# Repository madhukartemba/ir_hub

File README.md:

# IR Hub

A self-contained, open-source smart IR universal remote built around the ESP8266. IR Hub learns the codes from your existing TV/AC/audio remotes, stores them locally, and lets you fire them from a physical button, an on-device menu, Home Assistant (MQTT), or Alexa — all over your home Wi-Fi.

It ships as a complete hardware + firmware project: custom KiCad PCB, 3D-printed enclosure, and PlatformIO firmware with OTA updates.

- **Help (web preview):** https://ir-hub.pages.dev/help
- **Help (markdown source):** [`docs/HELP.md`](docs/HELP.md)
- **Release / OTA notes:** [`docs/RELEASE.md`](docs/RELEASE.md)

---

## What It Does

- **Learns IR remotes.** Point any IR remote at the receiver, press a button, and the Hub stores the raw signal.
- **Replays IR commands.** 8x parallel high-current IR LEDs give very long range so the Hub can sit across the room from the appliance.
- **Smart home bridge.** Each learned device shows up as an MQTT entity (works great with Home Assistant) and as an Alexa-controllable device (via Espalexa).
- **Standalone UI.** 128x64 OLED + single button + 30-LED NeoPixel ring + haptic motor + buzzer. No phone required for day-to-day use.
- **Captive-portal Wi-Fi setup.** First boot exposes an `IRHub V3 Setup` AP; users join it and configure Wi-Fi + MQTT from their phone.
- **OTA updates.** Cloud OTA (via Cloudflare Pages manifest, polled hourly) and LAN OTA (ArduinoOTA + mDNS auto-discovery).
- **Safe boot.** Boot-loop counter + LittleFS format-on-failure recovery so a bad save never bricks the device.

---

## Hardware Variants

**Only `v3` (the custom PCB build) is actively supported.** The older `v0` (NodeMCU perfboard) and `v1` (D1 Mini perfboard) variants still exist in the codebase as historical prototypes, but they are **deprecated** — no longer maintained, no longer released, and not recommended for new builds.

The rest of this README only covers v3.

---

## Bill of Materials (v3)

Full BOM with LCSC-style designators lives in [`PCB/IRHub_PCB_V3/production/bom.csv`](PCB/IRHub_PCB_V3/production/bom.csv). The major active parts:

| Block | Part | Role |
|---|---|---|
| MCU | **ESP-12F** (ESP8266) | Brains + Wi-Fi |
| USB | **USB-C receptacle + CH340C** | USB-UART for programming and 5 V power |
| Power | **AMS1117-3.3** LDO | 5 V -> 3.3 V regulation |
| Display | **OLED-128O064D** (SH1106, I²C) | 128x64 status/menu screen |
| LEDs | **30x WS2812B-2020** | Circular addressable RGB ring |
| IR TX | **8x IR204A** + UMH3N driver + AO3400A MOSFET | High-current IR blaster array |
| IR RX | **TSOP382xx** | 38 kHz IR demodulator for learning |
| Haptics | **DRV2605L** + external LRA (JST connector) | Tactile click feedback |
| Audio | **CMT-7525-80-SMT-TR** magnetic buzzer | UI beeps / chimes |
| Input | **Single tactile push button** | All UI navigation |

Plus passives, test points, and the JST-SH connector for the LRA.

---

## How To Build One (v3)

### 1. Order the PCB

KiCad project: [`PCB/IRHub_PCB_V3/`](PCB/IRHub_PCB_V3/)

- Source schematic + board: `IRHub_V3.kicad_sch`, `IRHub_V3.kicad_pcb`
- Manufacturing bundle: [`PCB/IRHub_PCB_V3/production/IR_Hub_3.zip`](PCB/IRHub_PCB_V3/production/IR_Hub_3.zip) (gerbers + drills, ready to upload to JLCPCB / PCBWay / OSHPark)
- For JLCPCB-style PCBA also use: `production/bom.csv` + `production/positions.csv`
- 3D preview / STEP: `IRHub_V3.step` and `IRHub_V3_Model.step`

Default board specs are 2-layer, 1.6 mm, HASL — anything in that ballpark from any low-cost fab works fine.

### 2. Print the Enclosure

3D-printable enclosure parts for the v3 PCB live in [`3D Print/Version 3/`](3D%20Print/Version%203/):

- `Base.stl` — main housing the PCB drops into
- `Top Cover.stl` — top shell with the OLED + button cutouts
- `Led Ring.stl` — diffuser ring that sits over the WS2812 ring

Plus the full Fusion 360 source as `IR Hub V3 v74.f3z`, and ready-to-print GCode under `3D Print/Version 3/GCode/`.

Recommended print settings: PLA, 0.2 mm layer height, 15–20% infill, supports off for `Top Cover` (geometry is overhang-friendly).

### 3. Assemble

1. Solder the PCB (or order PCBA). If hand-soldering, start with the QFP / SMD parts (CH340C, AMS1117, DRV2605L), then passives, then through-hole IR LEDs and the button, then the WS2812 ring last so it doesn't get cooked.
2. Verify 3.3 V on test point `TP9` and 5 V on `5V1` *before* installing the ESP-12F.
3. Solder/clip in the OLED, plug the LRA into the JST-SH connector.
4. Drop the populated PCB into the printed `Base`, screw on `Top Cover`, slip `Led Ring` over the LEDs.

### 4. Flash the Firmware

You only need to do this once — after that, OTA updates take over.

1. Install **PlatformIO** (VS Code extension or `pip install platformio`).
2. Clone this repo and open it in PlatformIO.
   ```bash
   git clone https://github.com/madhukartemba/ir_hub.git
   cd ir_hub
   ```
3. Create your `include/secrets.h` from the template:
   ```bash
   cp include/secrets.h.example include/secrets.h
   ```
   Edit it to set (all optional, but recommended):
   - `MQTT_HOST` / `MQTT_USER` / `MQTT_PASSWORD` — Home Assistant broker.
   - `OTA_PASSWORD` — required for LAN OTA pushes.
   - `OTA_MANIFEST_URL` — your Cloudflare Pages manifest URL (only needed if you fork and self-host releases).
4. Plug the assembled board into USB-C and run:
   ```bash
   pio run -e ir_hub_version_3 -t upload
   ```
5. Open the serial monitor to see boot logs:
   ```bash
   pio device monitor -b 115200
   ```

That's it — the rest of the configuration (Wi-Fi, MQTT credentials, learned remotes) happens on-device.

### 5. Power On & Configure

On first boot the Hub shows `IR Hub — Ready! (Offline)` and starts a captive-portal AP called **`IRHub V3 Setup`**. Connect a phone to it and the captive portal walks you through Wi-Fi (and optional MQTT) setup. From there, see the [User Help Guide](docs/HELP.md) for adding remotes, using Alexa, etc.

---

## Pinout (v3)

For reference, defined in [`src/config.h`](src/config.h):

| Function | ESP-12F Pin |
|---|---|
| Button | D0 |
| OLED SCL | D1 |
| OLED SDA | D2 |
| Buzzer | D3 |
| IR Receiver | D5 |
| IR Transmitter | D6 |
| NeoPixel ring | D7 |

---

## Project Layout

```
ir_hub/
  src/                Firmware entry + UI screens
  lib/                Internal libraries (IR, MQTT, Display, OtaUpdater, etc.)
  include/            Project headers + secrets template
  PCB/                KiCad sources + gerbers + production BOM (v3; v1 archived)
  3D Print/           Fusion sources + STL + GCode for enclosures
  docs/               User help, release/OTA documentation
  scripts/            Release automation + local OTA upload helper
  ota/                Public OTA manifest served via Cloudflare Pages
  binaries/           Signed firmware images served via Cloudflare Pages
```

---

## For Developers

All commands target v3 — the older `v0` / `v1` PlatformIO envs are deprecated and not part of the release pipeline.

- **Build:** `pio run -e ir_hub_version_3`
- **Cut a release:** `python3 scripts/release.py 1.2.3` — bumps `custom_firmware_version`, builds `ir_hub_version_3`, stages the binary under `binaries/`, updates `ota/manifest.json`, commits + pushes. See [`docs/RELEASE.md`](docs/RELEASE.md) for the full flow.
- **LAN OTA push:** `python3 scripts/local_upload_ota.py -e ir_hub_version_3 --discover` — mDNS-discovers `ir-hub-*` devices and pushes the current build over the network. Password is read from `include/secrets.h`.

---

## License

MIT — see `LICENSE` (or use the source freely; attribution appreciated).

---

<div align="center">
  Made by <a href="mailto:madhusmiles.madhukar@gmail.com">Madhukar Temba</a>
</div>

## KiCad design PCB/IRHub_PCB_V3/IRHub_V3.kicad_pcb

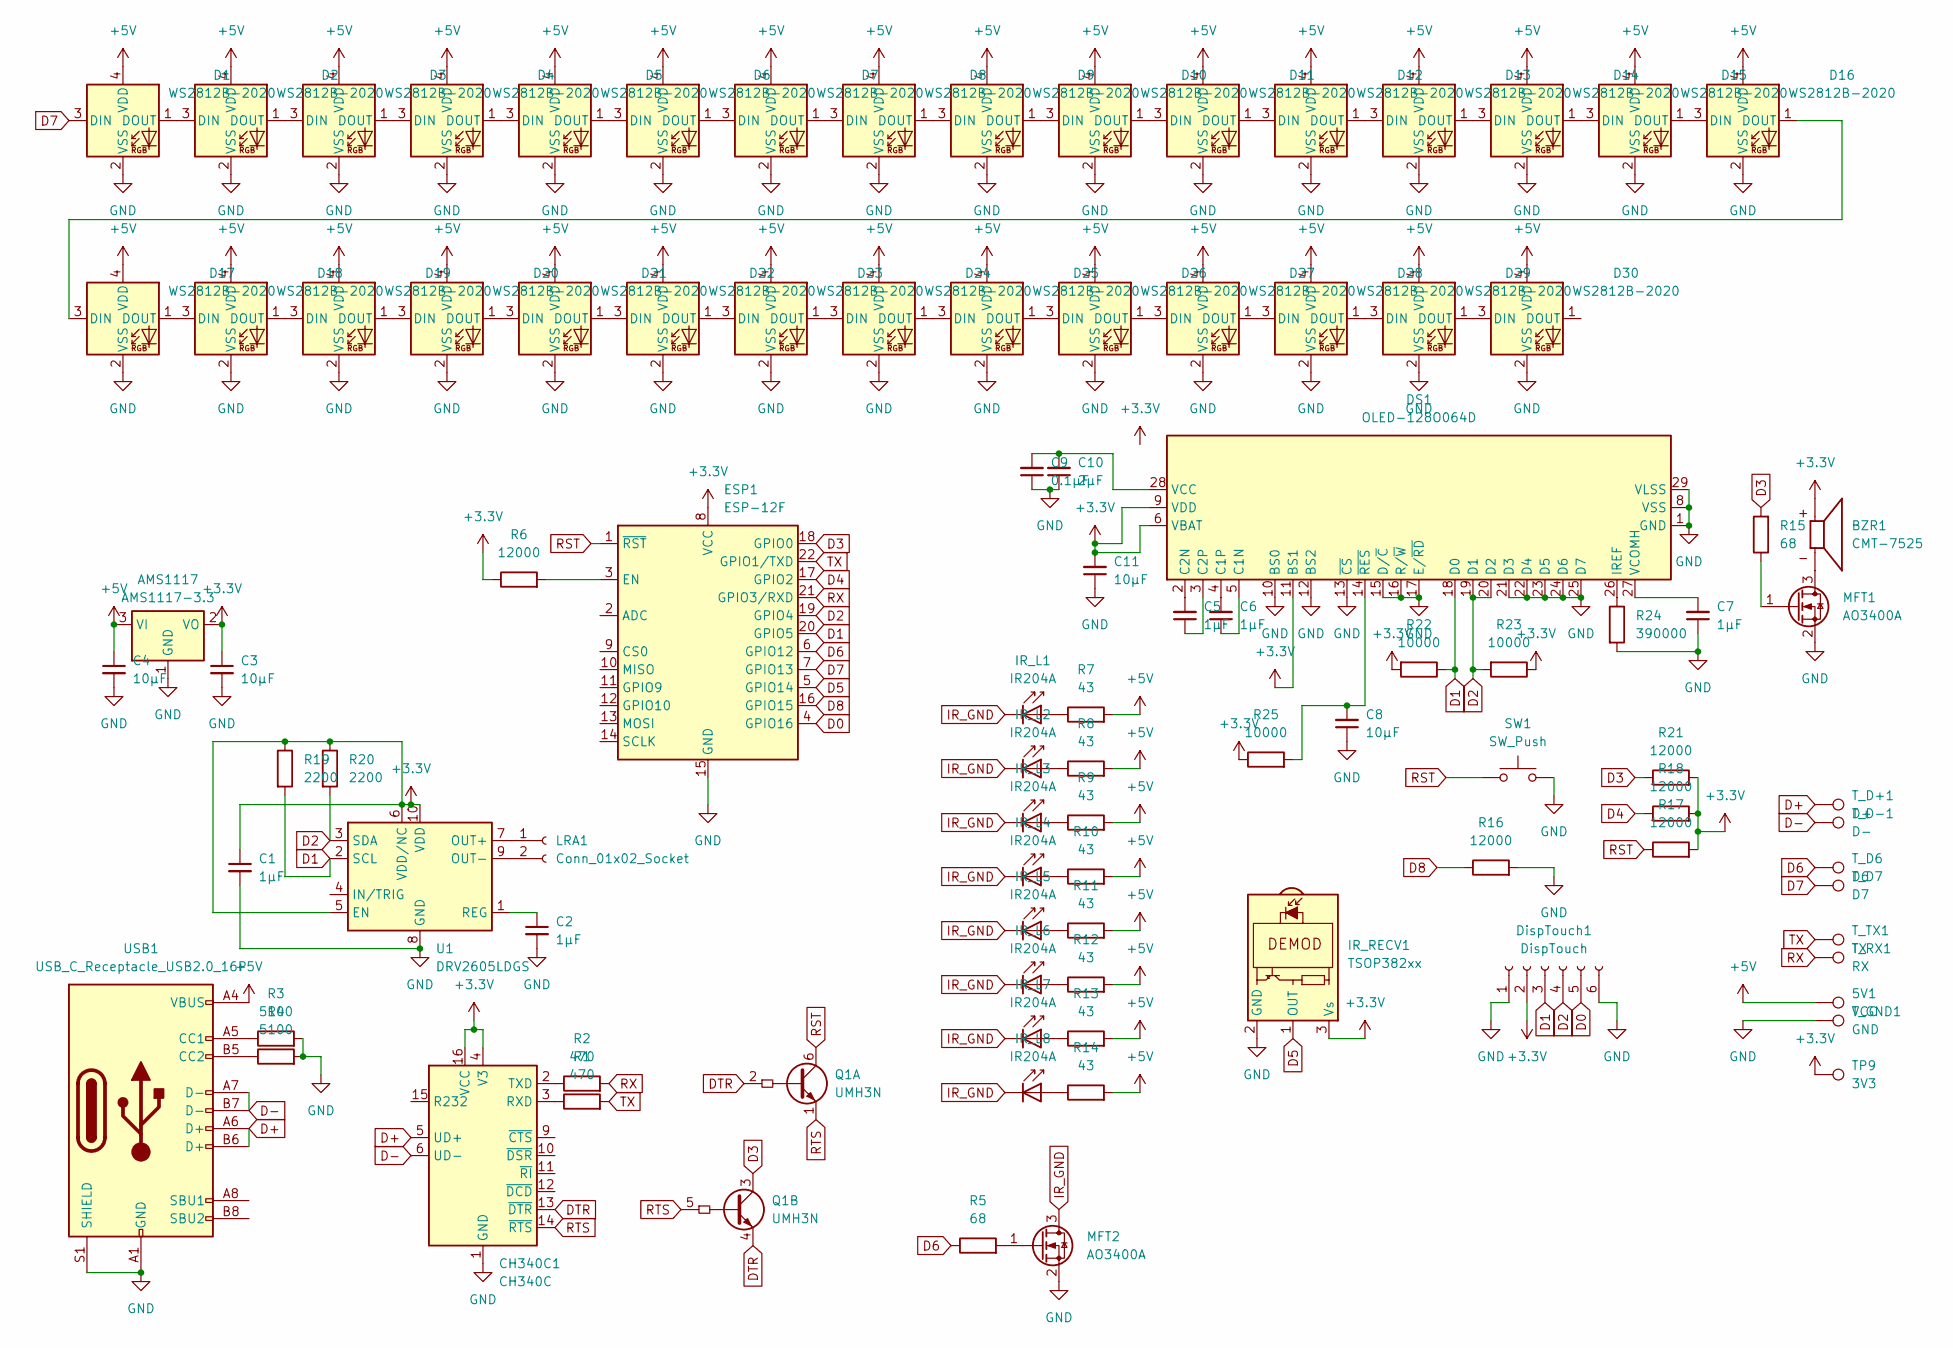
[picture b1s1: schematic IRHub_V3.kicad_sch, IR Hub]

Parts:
5V1: VCC; TestPoint_Pad_D1.0mm
AMS1117: AMS1117-3.3; SOT-223-3_TabPin2
BZR1: CMT-7525; XDCR_CMT-7525-80-SMT-TR; PARTREV N/A
C1, C2, C5, C6, C7: 1µF; C_0805_2012Metric_Pad1.18x1.45mm_HandSolder
C3, C4: 10µF; C_1206_3216Metric_Pad1.33x1.80mm_HandSolder
C8, C11: 10µF; C_0805_2012Metric_Pad1.18x1.45mm_HandSolder
C9: 0.1µF; C_0805_2012Metric_Pad1.18x1.45mm_HandSolder
C10: 2µF; C_0805_2012Metric_Pad1.18x1.45mm_HandSolder
CH340C1: CH340C; SOIC-16_3.9x9.9mm_P1.27mm
D1, D2, D3, D4, D5, D6, D7, D8, D9, D10, D11, D12, D13, D14, D15, D16, D17, D18, D19, D20, D21, D22, D23, D24, D25, D26, D27, D28, D29, D30: WS2812B-2020; LED_WS2812B-2020_PLCC4_2.0x2.0mm
DS1: OLED-128O064D
DispTouch1: DispTouch; JST_SH_BM06B-SRSS-TB_1x06-1MP_P1.00mm_Vertical
ESP1: ESP-12F; ESP-12E
IR_L1, IR_L2, IR_L3, IR_L4, IR_L5, IR_L6, IR_L7, IR_L8: IR204A; LED_D3.0mm_IRBlack
IR_RECV1: TSOP382xx; Vishay_MINICAST-3Pin
LRA1: Conn_01x02_Socket; PinHeader_1x02_P2.00mm_Vertical
MFT1, MFT2: AO3400A; SOT-23
Q1: UMH3N; SOT-363_SC-70-6
R1, R2: 470; R_1206_3216Metric
R3, R4: 5100; R_1206_3216Metric
R5, R15: 68; R_1206_3216Metric_Pad1.30x1.75mm_HandSolder
R6, R16, R17, R18, R21: 12000; R_1206_3216Metric_Pad1.30x1.75mm_HandSolder
R7, R8, R9, R10, R11, R12, R13, R14: 43; R_1210_3225Metric_Pad1.30x2.65mm_HandSolder
R19, R20: 2200; R_0805_2012Metric_Pad1.20x1.40mm_HandSolder
R22, R23, R25: 10000; R_0805_2012Metric_Pad1.20x1.40mm_HandSolder
R24: 390000; R_0805_2012Metric_Pad1.20x1.40mm_HandSolder
SW1: SW_Push; SW_SPST_TS-1088-xR020
TP9: 3V3; TestPoint_Pad_D1.0mm
T_D6: D6; TestPoint_Pad_D1.0mm
T_D7: D7; TestPoint_Pad_D1.0mm
T_D+1: D+; TestPoint_Pad_D1.0mm
T_D-1: D-; TestPoint_Pad_D1.0mm
T_GND1: GND; TestPoint_Pad_D1.0mm
T_RX1: RX; TestPoint_Pad_D1.0mm
T_TX1: TX; TestPoint_Pad_D1.0mm
U1: DRV2605LDGS; VSSOP-10_3x3mm_P0.5mm
USB1: USB_C_Receptacle_USB2.0_16P; USB_C_Receptacle_GCT_USB4110

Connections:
+3.3V: AMS1117.2 (VO), BZR1.P, C1.1, C3.1, C11.2, CH340C1.4 (V3), CH340C1.16 (VCC), DS1.6 (VBAT), DS1.9 (VDD), DS1.11 (BS1), DispTouch1.2, ESP1.8 (VCC), IR_RECV1.3 (Vs), R6.1, R17.2, R18.2, R19.1, R20.1, R21.2, R22.2, R23.1, R25.1, TP9.1, U1.5 (EN), U1.6 (VDD/NC), U1.10 (VDD)
+5V: 5V1.1, AMS1117.3 (VI), C4.1, D1.4 (VDD), D2.4 (VDD), D3.4 (VDD), D4.4 (VDD), D5.4 (VDD), D6.4 (VDD), D7.4 (VDD), D8.4 (VDD), D9.4 (VDD), D10.4 (VDD), D11.4 (VDD), D12.4 (VDD), D13.4 (VDD), D14.4 (VDD), D15.4 (VDD), D16.4 (VDD), D17.4 (VDD), D18.4 (VDD), D19.4 (VDD), D20.4 (VDD), D21.4 (VDD), D22.4 (VDD), D23.4 (VDD), D24.4 (VDD), D25.4 (VDD), D26.4 (VDD), D27.4 (VDD), D28.4 (VDD), D29.4 (VDD), D30.4 (VDD), R7.2, R8.2, R9.2, R10.2, R11.2, R12.2, R13.2, R14.2, USB1.A4 (VBUS), USB1.A9 (VBUS), USB1.B4 (VBUS), USB1.B9 (VBUS)
D0: DispTouch1.5, ESP1.4 (GPIO16)
D1: DS1.18 (D0), DispTouch1.3, ESP1.20 (GPIO5), R19.2, R22.1, U1.2 (SCL)
D2: DS1.19 (D1), DS1.20 (D2), DispTouch1.4, ESP1.19 (GPIO4), R20.2, R23.2, U1.3 (SDA)
D3: ESP1.18 (GPIO0), Q1.3 (C2), R15.2, R21.1
D4: ESP1.17 (GPIO2), R18.1
D5: ESP1.5 (GPIO14), IR_RECV1.1 (OUT)
D6: ESP1.6 (GPIO12), R5.1, T_D6.1
D7: D1.3 (DIN), ESP1.7 (GPIO13), T_D7.1
D8: ESP1.16 (GPIO15), R16.1
D+: CH340C1.5 (UD+), T_D+1.1, USB1.A6 (D+), USB1.B6 (D+)
D-: CH340C1.6 (UD-), T_D-1.1, USB1.A7 (D-), USB1.B7 (D-)
DTR: CH340C1.13 (~DTR), Q1.2 (B1), Q1.4 (E2)
GND: AMS1117.1 (GND), C1.2, C2.2, C3.2, C4.2, C7.1, C8.1, C9.1, C10.1, C11.1, CH340C1.1 (GND), D1.2 (VSS), D2.2 (VSS), D3.2 (VSS), D4.2 (VSS), D5.2 (VSS), D6.2 (VSS), D7.2 (VSS), D8.2 (VSS), D9.2 (VSS), D10.2 (VSS), D11.2 (VSS), D12.2 (VSS), D13.2 (VSS), D14.2 (VSS), D15.2 (VSS), D16.2 (VSS), D17.2 (VSS), D18.2 (VSS), D19.2 (VSS), D20.2 (VSS), D21.2 (VSS), D22.2 (VSS), D23.2 (VSS), D24.2 (VSS), D25.2 (VSS), D26.2 (VSS), D27.2 (VSS), D28.2 (VSS), D29.2 (VSS), D30.2 (VSS), DS1.1 (GND), DS1.8 (VSS), DS1.10 (BS0), DS1.12 (BS2), DS1.13 (~CS), DS1.15 (D/~C), DS1.16 (R/~W), DS1.17 (E/~RD), DS1.21 (D3), DS1.22 (D4), DS1.23 (D5), DS1.24 (D6), DS1.25 (D7), DS1.29 (VLSS), DS1.30 (GND), DispTouch1.1, DispTouch1.6, ESP1.15 (GND), IR_RECV1.2 (GND), MFT1.2 (S), MFT2.2 (S), R3.2, R4.2, R16.2, R24.2, SW1.2, T_GND1.1, U1.8 (GND), USB1.A1 (GND), USB1.A12 (GND), USB1.B1 (GND), USB1.B12 (GND), USB1.S1 (SHIELD)
IR_GND: IR_L1.1 (K), IR_L2.1 (K), IR_L3.1 (K), IR_L4.1 (K), IR_L5.1 (K), IR_L6.1 (K), IR_L7.1 (K), IR_L8.1 (K), MFT2.3 (D)
unnamed: CH340C1.3 (RXD), R1.1
unnamed: CH340C1.2 (TXD), R2.1
unnamed: D1.1 (DOUT), D2.3 (DIN)
unnamed: D2.1 (DOUT), D3.3 (DIN)
unnamed: D3.1 (DOUT), D4.3 (DIN)
unnamed: D4.1 (DOUT), D5.3 (DIN)
unnamed: D5.1 (DOUT), D6.3 (DIN)
unnamed: D6.1 (DOUT), D7.3 (DIN)
unnamed: D7.1 (DOUT), D8.3 (DIN)
unnamed: D8.1 (DOUT), D9.3 (DIN)
unnamed: D9.1 (DOUT), D10.3 (DIN)
unnamed: D10.1 (DOUT), D11.3 (DIN)
unnamed: D11.1 (DOUT), D12.3 (DIN)
unnamed: D12.1 (DOUT), D13.3 (DIN)
unnamed: D13.1 (DOUT), D14.3 (DIN)
unnamed: D14.1 (DOUT), D15.3 (DIN)
unnamed: D15.1 (DOUT), D16.3 (DIN)
unnamed: D16.1 (DOUT), D17.3 (DIN)
unnamed: D17.1 (DOUT), D18.3 (DIN)
unnamed: D18.1 (DOUT), D19.3 (DIN)
unnamed: D19.1 (DOUT), D20.3 (DIN)
unnamed: D20.1 (DOUT), D21.3 (DIN)
unnamed: D21.1 (DOUT), D22.3 (DIN)
unnamed: D22.1 (DOUT), D23.3 (DIN)
unnamed: D23.1 (DOUT), D24.3 (DIN)
unnamed: D24.1 (DOUT), D25.3 (DIN)
unnamed: D25.1 (DOUT), D26.3 (DIN)
unnamed: D26.1 (DOUT), D27.3 (DIN)
unnamed: D27.1 (DOUT), D28.3 (DIN)
unnamed: D28.1 (DOUT), D29.3 (DIN)
unnamed: D29.1 (DOUT), D30.3 (DIN)
unnamed: C6.1, DS1.5 (C1N)
unnamed: C6.2, DS1.4 (C1P)
unnamed: C5.2, DS1.2 (C2N)
unnamed: C5.1, DS1.3 (C2P)
unnamed: DS1.26 (IREF), R24.1
unnamed: C9.2, C10.2, DS1.28 (VCC)
unnamed: C7.2, DS1.27 (VCOMH)
unnamed: C8.2, DS1.14 (~RES), R25.2
unnamed: ESP1.3 (EN), R6.2
unnamed: IR_L1.2 (A), R7.1
unnamed: IR_L2.2 (A), R8.1
unnamed: IR_L3.2 (A), R9.1
unnamed: IR_L4.2 (A), R10.1
unnamed: IR_L5.2 (A), R11.1
unnamed: IR_L6.2 (A), R12.1
unnamed: IR_L7.2 (A), R13.1
unnamed: IR_L8.2 (A), R14.1
unnamed: LRA1.1, U1.7 (OUT+)
unnamed: LRA1.2, U1.9 (OUT-)
unnamed: BZR1.N, MFT1.3 (D)
unnamed: MFT1.1 (G), R15.1
unnamed: MFT2.1 (G), R5.2
unnamed: C2.1, U1.1 (REG)
unnamed: R3.1, USB1.A5 (CC1)
unnamed: R4.1, USB1.B5 (CC2)
RST: ESP1.1 (~RST), Q1.6 (C1), R17.1, SW1.1
RTS: CH340C1.14 (~RTS), Q1.1 (E1), Q1.5 (B2)
RX: ESP1.21 (GPIO3/RXD), R2.2, T_RX1.1
TX: ESP1.22 (GPIO1/TXD), R1.2, T_TX1.1

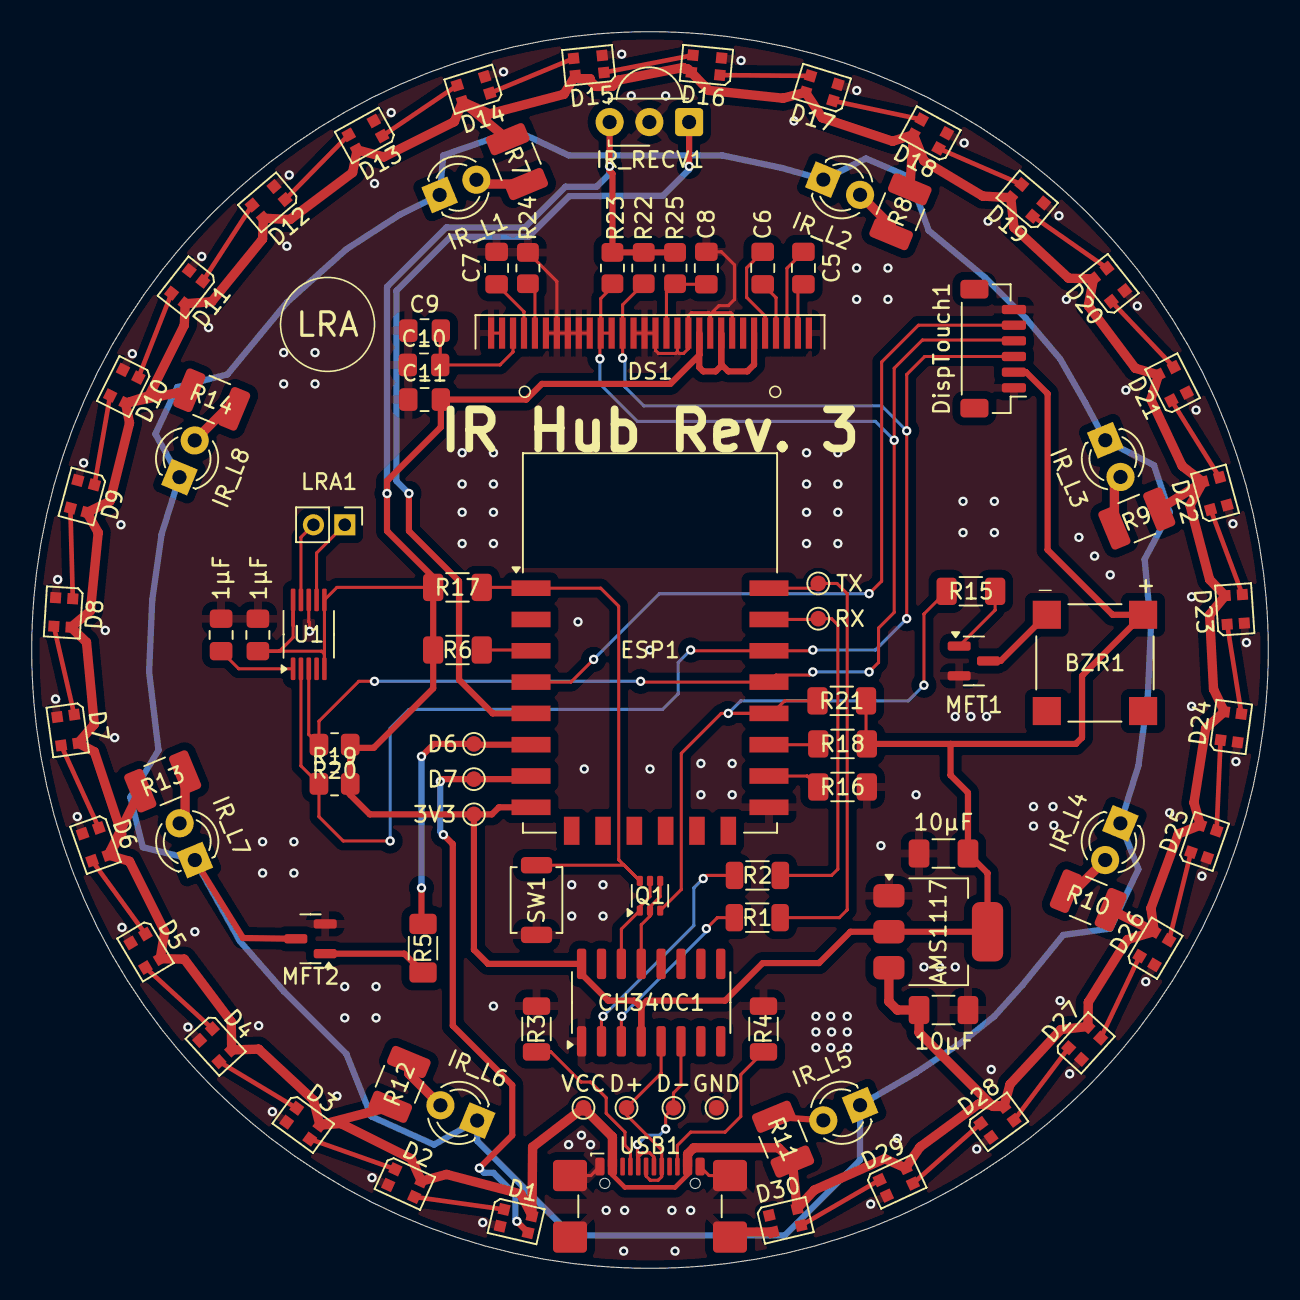
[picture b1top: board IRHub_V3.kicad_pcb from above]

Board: 2 copper layers, 79.0 x 79.0 mm, 97 parts (0 on the bottom side), 76 nets.

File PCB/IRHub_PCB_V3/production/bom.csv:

Designator,Footprint,Quantity,Value,LCSC Part #
5V1,TestPoint_Pad_D1.0mm,1,VCC,
AMS1117,SOT-223-3_TabPin2,1,AMS1117-3.3,
BZR1,XDCR_CMT-7525-80-SMT-TR,1,CMT-7525,
"C1, C2, C5, C6, C7",0805,5,1µF,
C10,0805,1,2µF,
"C11, C8",0805,2,10µF,
"C3, C4",1206,2,10µF,
C9,0805,1,0.1µF,
CH340C1,SOIC-16_3.9x9.9mm_P1.27mm,1,CH340C,
"D1, D10, D11, D12, D13, D14, D15, D16, D17, D18, D19, D2, D20, D21, D22, D23, D24, D25, D26, D27, D28, D29, D3, D30, D4, D5, D6, D7, D8, D9",LED_WS2812B-2020_PLCC4_2.0x2.0mm,30,WS2812B-2020,
DISPTOUCH1,JST_SH_BM06B-SRSS-TB_1x06-1MP_P1.00mm_Vertical,1,DispTouch,
DS1,OLED-128O064D,1,OLED-128O064D,
ESP1,ESP-12E,1,ESP-12F,
"IR_L1, IR_L2, IR_L3, IR_L4, IR_L5, IR_L6, IR_L7, IR_L8",LED_D3.0mm_IRBlack,8,IR204A,
IR_RECV1,Vishay_MINICAST-3Pin,1,TSOP382xx,
LRA1,PinHeader_1x02_P2.00mm_Vertical,1,Conn_01x02_Socket,
"MFT1, MFT2",SOT-23,2,AO3400A,
Q1,SOT-363_SC-70-6,1,UMH3N,
"R1, R2",1206,2,470,
"R10, R11, R12, R13, R14, R7, R8, R9",1210,8,43,
"R15, R5",1206,2,68,
"R16, R17, R18, R21, R6",1206,5,12000,
"R19, R20",0805,2,2200,
"R22, R23, R25",0805,3,10000,
R24,0805,1,390000,
"R3, R4",1206,2,5100,
SW1,SW_SPST_TS-1088-xR020,1,SW_Push,
TP9,TestPoint_Pad_D1.0mm,1,3V3,
T_D+1,TestPoint_Pad_D1.0mm,1,D+,
T_D-1,TestPoint_Pad_D1.0mm,1,D-,
T_D6,TestPoint_Pad_D1.0mm,1,D6,
T_D7,TestPoint_Pad_D1.0mm,1,D7,
T_GND1,TestPoint_Pad_D1.0mm,1,GND,
T_RX1,TestPoint_Pad_D1.0mm,1,RX,
T_TX1,TestPoint_Pad_D1.0mm,1,TX,
U1,VSSOP-10_3x3mm_P0.5mm,1,DRV2605LDGS,
USB1,USB_C_Receptacle_GCT_USB4110,1,USB_C_Receptacle_USB2.0_16P,

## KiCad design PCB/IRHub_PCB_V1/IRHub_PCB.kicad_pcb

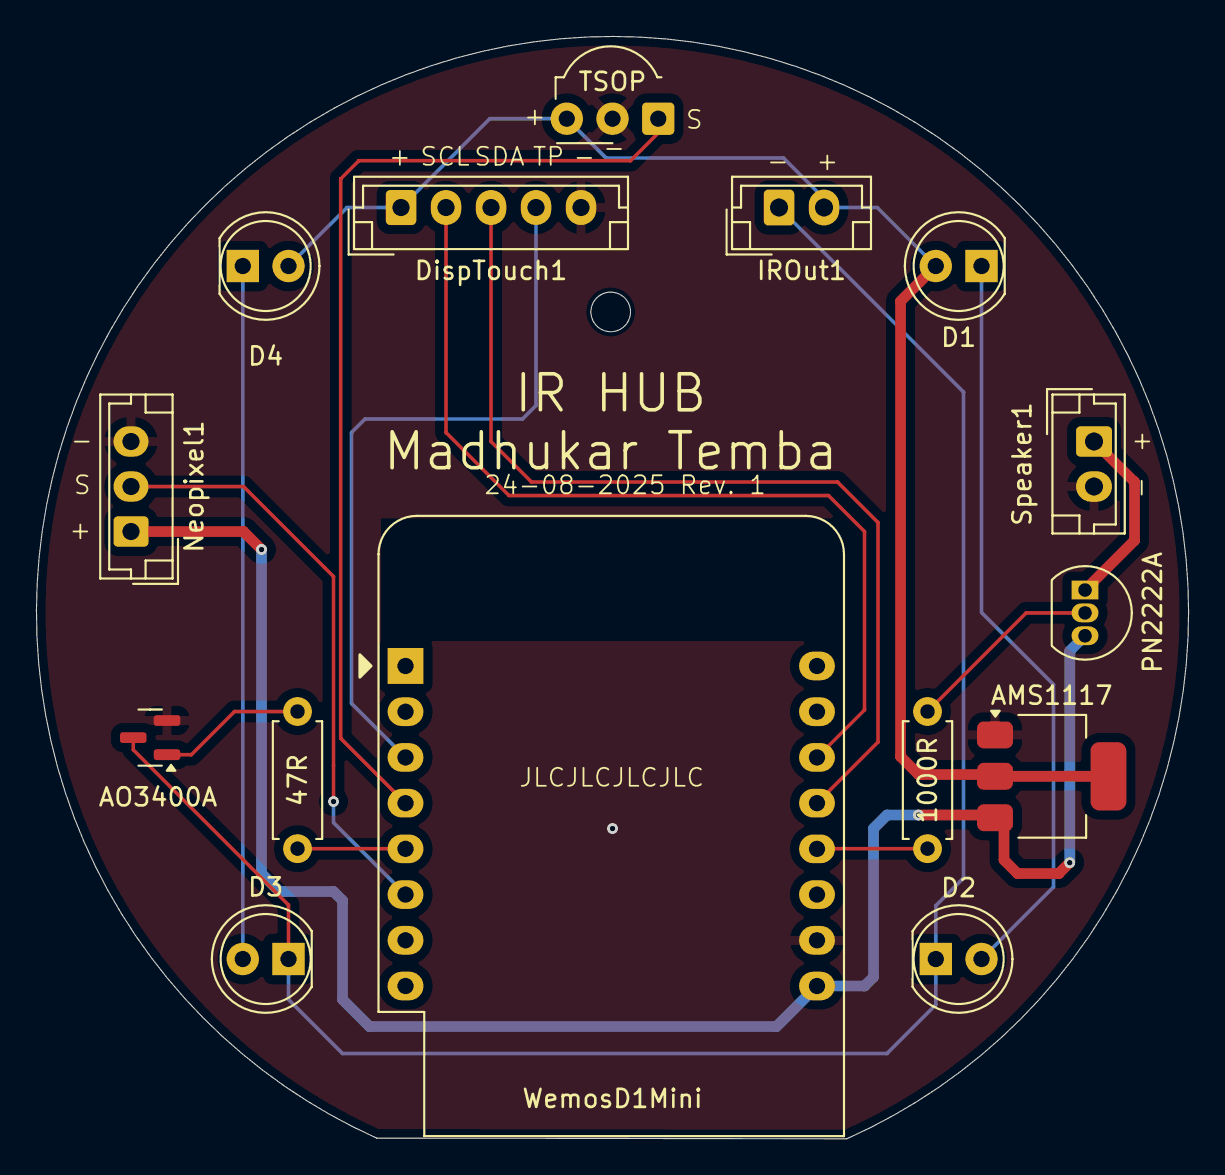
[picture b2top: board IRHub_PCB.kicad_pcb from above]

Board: 2 copper layers, 64.0 x 61.2 mm, 15 parts (0 on the bottom side), 16 nets.

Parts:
47R: 47; R_Axial_DIN0207_L6.3mm_D2.5mm_P7.62mm_Horizontal
1000R: 1000; R_Axial_DIN0207_L6.3mm_D2.5mm_P7.62mm_Horizontal
AMS1117: AMS1117-3.3; SOT-223-3_TabPin2
AO3400A: AO3400A; SOT-23
D1, D2, D3, D4: LD271; LED_D5.0mm_IRGrey
DispTouch1: Conn_01x05_Pin; JST_EH_B5B-EH-A_1x05_P2.50mm_Vertical
IROut1: Conn_01x02_Pin; JST_EH_B2B-EH-A_1x02_P2.50mm_Vertical
Neopixel1: Conn_01x03_Pin; JST_EH_B3B-EH-A_1x03_P2.50mm_Vertical
PN2222A: PN2222A; TO-92_Inline
Speaker1: Conn_01x02_Pin; JST_EH_B2B-EH-A_1x02_P2.50mm_Vertical
TSOP: TSOP43xx; Vishay_MOLD-3Pin
WemosD1Mini: WEMOS_D1_mini; WEMOS_D1_mini_light

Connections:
+3.3V: AMS1117.2 (VO), D1.2 (A), D4.2 (A), DispTouch1.1, IROut1.2, TSOP.3 (Vs)
+5V: AMS1117.3 (VI), Neopixel1.1, PN2222A.3 (C), WemosD1Mini.9 (5V)
GND: AMS1117.1 (GND), AO3400A.2 (S), DispTouch1.5, Neopixel1.3, Speaker1.2, TSOP.2 (GND), WemosD1Mini.10 (GND)
unnamed: D1.1 (K), D2.2 (A)
unnamed: AO3400A.3 (D), D2.1 (K), D3.1 (K), IROut1.1
unnamed: D3.2 (A), D4.1 (K)
unnamed: DispTouch1.2, WemosD1Mini.14 (SCL/D1)
unnamed: DispTouch1.3, WemosD1Mini.13 (SDA/D2)
unnamed: DispTouch1.4, WemosD1Mini.3 (D0)
unnamed: Neopixel1.2, WemosD1Mini.6 (MOSI/D7)
unnamed: 1000R.2, PN2222A.2 (B)
unnamed: PN2222A.1 (E), Speaker1.1
unnamed: 47R.2, AO3400A.1 (G)
unnamed: 1000R.1, WemosD1Mini.12 (D3)
unnamed: 47R.1, WemosD1Mini.5 (MISO/D6)
unnamed: TSOP.1 (OUT), WemosD1Mini.4 (SCK/D5)

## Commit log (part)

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2025-08-16 Revert "alexa"
    This reverts commit 1071f9ba4b69831fdbf9f1ddea8a3c6dd70972e6.
2025-08-16 play startup sound
2025-08-16 add alexa connector
2025-08-16 add device manager cache
2025-08-16 remove bad practices
2025-08-16 add cache by id as well
2025-08-16 more best practices
2025-08-16 fix compile issues
2025-08-16 add alexa connector to main
2025-08-16 add callbacks
2025-08-16 remove exceptions
2025-08-16 remove exceptions from idgen
2025-08-17 remove ir test from settings
2025-08-17 remove ir test hub
2025-08-17 add restarting option
2025-08-17 fix warnings
2025-08-17 new home screen
2025-08-17 remove :
2025-08-17 add reset wifi settings option
2025-08-17 add menu utils
2025-08-17 better ip ui
2025-08-17 ir hub alignment
2025-08-17 better bar
2025-08-17 center
2025-08-17 update wipe text
2025-08-17 add wifi text
2025-08-17 wifi manager ui
2025-08-17 add wifimanager lib
2025-08-17 remove param
2025-08-17 white text
2025-08-17 remove unnecessary changes
2025-08-17 use own wifi library
2025-08-19 fixed led lib
2025-08-19 demo changes
2025-08-19 add pulse anim
2025-08-19 remove demo code
2025-08-19 remove cpp wifi man file
2025-08-19 remove unused method
2025-08-19 also add ring
2025-08-19 fix warn
2025-08-19 async wifi manager
2025-08-19 debug mode
2025-08-19 Revert "debug mode"
    This reverts commit 3bc5fcf29b67e75cf5b1b3c985ca7e7fd12c602d.
2025-08-19 Revert "async wifi manager"
    This reverts commit 4e1f5cc59353b2cd6d1e210f9e9a104e8f7bf6f4.
2025-08-20 working pulse anim
2025-08-20 add solid mode
2025-08-20 add led anims
2025-08-20 fix router bug
2025-08-20 add animations
2025-08-20 update timeout
2025-08-20 change brightness
2025-08-20 speed change
2025-08-20 reduce speed
2025-08-20 brightness update
2025-08-20 add more colors
2025-08-20 Revert "brightness update"
    This reverts commit 2c54aee13f8c2fb88c9116516765839e1a5da18c.
2025-08-20 brightness transition
2025-08-20 fix breathe call
2025-08-20 use breathe effects
2025-08-20 add breathe
2025-08-20 color change
2025-08-20 smoother wave
2025-08-20 Revert "smoother wave"
    This reverts commit 5f6775662d3069c5791669afd63ccdc79e78ad03.
2025-08-20 Revert "color change"
    This reverts commit 7f7241c0891b37f0697d11de895fe009802f6c0c.
2025-08-20 Revert "add breathe"
    This reverts commit 91b74badbf92c4c97843835a1e4c254b16d5eb72.
2025-08-20 add royal blue color
2025-08-20 add pulse on ir
2025-08-20 change color
2025-08-20 add colors in menu send
2025-08-20 add desc
2025-08-20 remove page indicator
2025-08-20 change colora
2025-08-20 add return
2025-08-20 add preferences file
2025-08-20 remove unused code
2025-08-20 wifi manager fixes
2025-08-20 update colors
2025-08-20 change homescreen button behaviour
2025-08-20 remove extra logs
2025-08-20 changes to details page
2025-08-20 update click behaviour
2025-08-20 add timeout on router
2025-08-20 add router timeout
2025-08-20 add activity timeout functionality
2025-08-20 fix clear error hopefully
2025-08-20 fix clear error
2025-08-20 remove logs and fix clear method
2025-08-21 remove desc
2025-08-22 switch to espalexa
2025-08-22 add fauxmo alexa connector as well for future reference
2025-08-22 add comment
2025-08-22 add short beep
2025-08-22 change beeps;
2025-08-22 revert button sound
2025-08-22 add sounds
2025-08-22 add color
2025-08-22 add beeps in add device
2025-08-22 fix issues with id gen
2025-08-22 add more beeps
2025-08-22 log upgrade
2025-08-22 new log tests on alexa connector
2025-08-22 Revert "new log tests on alexa connector"
    This reverts commit bcfabeec72867758a578b9e219d1f6f941118590.
2025-08-22 Revert "log upgrade"
    This reverts commit 2294c85518ae1e8bc105a6726d1772d4ef5f4aeb.
2025-08-22 set device type
2025-08-22 fix fast led version
2025-08-22 Revert "fix fast led version"
    This reverts commit 05828b967562b2f1cf58f5daff040834bfbdcdff.
2025-08-24 add pcb file
2025-08-24 rename folder
2025-08-27 add step file
2025-08-27 change display lib
2025-08-27 fix alignment issue
2025-08-27 update font
2025-08-28 add base 3d print
2025-08-28 add new body
2025-08-28 update 3d file slightly
2025-08-28 add sh1106 support
2025-08-28 change ver
2025-08-28 add oled plate test
2025-08-28 add supports
2025-08-28 minor tweaks
2025-08-28 add ver 3
2025-08-28 remove old versions
2025-08-29 add version 4
2025-08-29 add logo
2025-08-29 add ver 4 files
2025-08-29 remove older versions
2025-08-29 ver 5 base
2025-08-29 add ver 5 supports
2025-08-29 rename files
2025-08-29 add f360 file
2025-08-29 split out envs
2025-08-29 update config
2025-08-29 display flip config
2025-08-29 add sno bases
2025-08-30 rename
2025-08-30 change num leds
2025-08-30 hieght update
2025-09-03 ui fixes
2025-09-03 position fixes
2025-09-03 text adj
2025-09-04 add ota upload script
2025-09-04 update max workers to 8
2025-09-13 add pcb v3
2025-09-13 complete schematic i think ?
2025-09-13 try to arrange leds in a circle
2025-09-14 final design i think
2025-09-14 added haptics
2025-09-14 power pcb done
2025-09-15 finished placement
2025-09-15 save all
2025-09-15 update resistor values
2025-09-15 complete pcb design
2025-09-15 final board design i hope
2025-09-15 added one missing res 👀
2025-09-15 generated gerber
2025-09-15 generate pcb using plugin
2025-09-15 some auto updates by kicad
2025-09-15 add ds store ignore
2025-09-22 fix pcb led issue :)
2025-09-22 new pcb
2025-09-22 add vias
2025-09-23 small space savings for the oled conn
2025-09-23 new updated version with oled connector
2025-09-23 final production build, hope I didn't mess something up this time :)
2025-09-27 add prototype 3d print file
2025-09-27 change resolution
2025-09-30 backup
2025-09-30 new 3d file
2025-09-30 add version 3
2025-10-01 fix oled connector wiring
2025-10-01 update stls
2025-10-01 added bulk gcode
2025-10-02 final 3d print files I hpe
2025-10-11 new ring library animation class
2025-10-11 add 4 anims
2025-10-11 add engine and driver
2025-10-11 add combiner and fader
2025-10-11 add engine logic
2025-10-11 add colors
2025-10-11 add neo ring
2025-10-11 fix issues
2025-10-11 fix issues hopefull
2025-10-11 add fast led driver
2025-10-11 update fastled version didn't fix anything though
2025-10-11 use neo driver
2025-10-11 small fixes
2025-10-11 add spinner
2025-10-11 fix wave
2025-10-12 add engine sleep
2025-10-12 switch to new led lib
2025-10-12 switch to solid color while recording
2025-10-12 working lib shift
2025-10-12 fin tran
2025-10-12 add min brightness to wave
2025-10-12 add fin tran to ota
2025-10-12 remove led ring lib
2025-10-12 try fixing fade err
2025-10-12 limit display frame rate
2025-10-12 reduce refresh rate on home screen
2025-10-12 remove on exit is blank
2025-10-12 add logs
2025-10-12 set monitor baud
2025-10-12 remove center led config
2025-10-12 change default fps to 15
2025-10-12 add display driver selection
2025-10-12 add blink command
2025-10-12 dark orange darker
2025-10-12 use blink
2025-10-12 change fps to 10
2025-10-12 use colors directly for on off
2025-10-12 add finish transition
2025-10-12 potentially fix finishtransition bug
2025-10-12 uipdaste comment
2025-10-13 switch to the git version of neo ring library
2025-10-21 add base top 2 gcode
2026-03-26 add basic connector impl
2026-03-26 use mac
2026-03-26 add mqtt
2026-03-26 working mqtt config
2026-03-26 upgrade ver
2026-03-27 revert changes
2026-03-27 add ext
2026-03-28 add haptics
2026-03-28 haptics working check
2026-03-28 fix stuck pixel issue in v3
2026-03-28 change interval
2026-04-29 fix ac state bug
2026-05-01 add click anim
2026-05-01 use sweep anim
2026-05-01 update callbacks
2026-05-01 update color
2026-05-23 update mqtt config
2026-05-23 memory leak fixes
2026-05-23 fix boot loop delay and attempt recovery
2026-05-23 nice to have features
2026-05-23 haptics en
2026-05-23 disbale haptic cali on boot
2026-05-23 fix warning
2026-05-23 fix long press during rec issue
2026-05-23 log changes
2026-05-23 fix back issue
2026-05-23 add debug logs
2026-05-23 remove debug logs
2026-05-23 display optimisations
2026-05-23 remove large comments
2026-05-23 update fps
2026-05-23 ota update test
2026-05-23 add release md
2026-05-23 fix updater
2026-05-23 update release
2026-05-23 chore(release): v1.0.1
2026-05-23 update updater
2026-05-23 chore(release): v1.0.2
2026-05-23 change heap req
2026-05-23 chore(release): v1.0.3
2026-05-23 update ini
2026-05-23 fix releases
2026-05-23 edit
2026-05-23 chore(release): v1.0.4
2026-05-23 chore(release): v1.0.5
2026-05-23 chore(release): v1.0.6
2026-05-24 chore(release): v1.0.7
2026-05-24 update releaser
2026-05-24 chore(release): v1.0.8
2026-05-24 chore(release): v1.0.9
2026-05-24 chore(release): v1.0.10
2026-05-24 chore(release): v1.0.11
2026-05-24 chore(release): v1.0.12
2026-05-24 chore(release): v1.0.13
2026-05-24 chore(release): v1.0.14
2026-05-24 Revert "chore: update manifest URL and comments for GitHub Releases"
    This reverts commit c4a64284319bab9f30dcdee60c16f519254f0bf5.
2026-05-24 Revert "chore(release): v1.0.14"
    This reverts commit 546b247068d25b8682ca6c17e1fddec020ef7a6e.
2026-05-24 Revert "feat: switch OTA back to GitHub Releases with redirect handling"
    This reverts commit ef2333637cb7edf1bdd685e1d4b73900a7fe5fee.
2026-05-24 structure
2026-05-24 update release file
2026-05-24 ignore pycache
2026-05-24 change text
2026-05-24 improve settings ux
2026-05-24 show qr
2026-05-24 add qr and authoer info
2026-05-24 new ota updater
2026-05-24 update ota py
2026-05-24 move ota file
2026-05-24 update ota bar
2026-05-24 improve update ui
2026-05-24 add factory reset capability
2026-05-24 improve settngs menu
2026-05-24 add easter egg
2026-05-24 update easter egg
2026-05-24 increase upload speed
2026-05-24 decrease upload speed
2026-05-24 update anims
2026-05-24 add wifi reset confirmation
2026-05-24 adjust text pos
2026-05-24 add help docs
2026-05-24 add mqtt info
2026-05-24 slightly lower heap thresh
2026-05-24 chore(release): v1.1.0
2026-05-24 update qr
2026-05-24 chore(release): v1.1.1
2026-05-24 improve help md file
2026-05-24 improve help md
2026-05-24 chore(release): v1.1.2
2026-05-24 remove comment
2026-05-24 add gcode
2026-05-24 add ota manifest url
2026-05-24 update main menu
2026-05-24 chore(release): v1.2.0
2026-05-24 mqtt improvements
2026-05-24 remove device cache
2026-05-24 use low mem mode
2026-05-24 memory improvements
2026-05-24 chore(release): v1.2.1
2026-05-24 use fastled for v0
2026-05-24 chore(release): v1.2.2
2026-05-25 add setup menu
2026-05-25 switch driver
2026-05-25 fix wifi red col
2026-05-25 update logo
2026-05-25 enable alexa after wifi connection
2026-05-25 update order
2026-05-25 update mqtt conn for diag info
2026-05-25 fix info screen
2026-05-25 add ha diag
2026-05-25 chore(release): v1.2.3
2026-05-25 experimental test
2026-05-25 local alexa lib
2026-05-26 alexa udp changes
2026-05-26 update pio
2026-05-26 chore(release): v1.2.4
2026-05-26 uuid test
2026-05-26 working espalexa finally
2026-05-26 remove comments
2026-05-26 remove big comments
2026-05-26 remove older binaries
2026-05-26 update help docs
2026-05-26 fix setup selection
2026-05-26 fix onboarding screen
2026-05-26 update wifi manager
2026-05-26 update wifi connection behav
2026-05-26 update intro
2026-05-26 revamped home ui
2026-05-26 update anim
2026-05-26 ui revamp
2026-05-26 update mqtt stat
2026-05-26 increase ap timeout
2026-05-26 state fix
2026-05-26 sync device state
2026-05-26 fix retry bug
2026-05-26 optimise ram
2026-05-27 reduce ram usage
2026-05-29 new top cover
2026-05-30 3d print update
2026-05-30 3d print v100
2026-06-01 update stl
2026-06-01 update 3d print
2026-06-09 chore(release): v2.0.0
